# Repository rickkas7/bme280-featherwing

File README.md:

# BME280 FeatherWing with Grove

*FeatherWing with a BME280 temperature, humidity, and pressure sensor. And Grove connectors.*

This is a simple board that includes a BME280 temperature, humidity, and pressure sensor, connected by I2C (pins D0 and D1). Since the chip is really tiny, it also includes [Grove connectors](http://wiki.seeedstudio.com/Grove_System/) so you can attach other analog, digital, or I2C sensors with a 4-pin Grove cable.

## What You Need

This is a somewhat advanced project mainly because the BME280 is tiny and has pads on the bottom of the module, making it impossible to solder by hand. You'll need a SMD reflow oven to do it effectively.

- Circuit boards (I order them from [OshPark](https://oshpark.com))
- Stencil (this board can be assembled without one, but I order them from [OshStencils](https://oshstencils.com))
- Solder paste
- Reflow oven (the inexpensive [T962](https://www.amazon.com/dp/B01LZYEF90/ref=dp_prsubs_1) works fine)
- Soldering iron (for the header pins and Grove connectors)
- Regular solder

## Eagle Directory

- FeatherBME280.sch Schematic for Eagle CAD (also available in pdf)
- FeatherBME280.pdf Schematic in pdf
- FeatherBME280.brd Board Layout in Eagle CAD
- FeatherBME280.lbr Library file with all components in the board

## BOM

| Quantity | Item | Example |
| --- | --- | --- |
| 1 | 0.1µF capacitor 0603 | [Murata GRM188R71C104KA01D](https://www.digikey.com/product-detail/en/murata-electronics-north-america/GRM188R71C104KA01D/490-1532-1-ND/587771) |
| 2 | 10KΩ resistor 0603 | [Panasonic ERJ-PA3J103V](https://www.digikey.com/product-detail/en/panasonic-electronic-components/ERJ-PA3J103V/P10KBZCT-ND/5036237) | 
| 1 | BME280 | [BME280](https://www.digikey.com/product-detail/en/bosch-sensortec/BME280/828-1063-1-ND/6136314) |
| 4 | Grove Connectors | [Grove connector](https://www.digikey.com/product-detail/en/seeed-technology-co-ltd/110990030/1597-1082-ND/5482560) |
| | Male header pins 0.1" | [Sullins PRPC040SAAN-RC](https://www.digikey.com/product-detail/en/PRPC040SAAN-RC/S1011EC-40-ND/2775214) |

## Firmware

In order to use the BME280 sensor, you can use the [Adafruit\_BME280\_RK](https://github.com/rickkas7/Adafruit_BME280_RK) library. Follow the i2c_bme280 example as this board uses the BME280 in I2C mode.

Example:

```
#include "Adafruit_BME280_RK.h"

#define SEALEVELPRESSURE_HPA (1013.25)

Adafruit_BME280 bme; // I2C

unsigned long delayTime;

void printValues();

void setup() {
    Serial.begin(9600);
    Serial.println("BME280 test");

    bool status;
    
    // Address is either 0x76 or 0x77. If omitted, the default is 0x77.
    status = bme.begin(0x76);
    if (!status) {
        Serial.println("Could not find a valid BME280 sensor, check wiring!");
        while (1);
    }
    
    Serial.println("-- Default Test --");
    delayTime = 1000;

    Serial.println();
}

void loop() { 
    printValues();
    delay(delayTime);
}

void printValues() {
    Serial.print("Temperature = ");
    Serial.print(bme.readTemperature());
    Serial.println(" *C");

    Serial.print("Pressure = ");

    Serial.print(bme.readPressure() / 100.0F);
    Serial.println(" hPa");

    Serial.print("Approx. Altitude = ");
    Serial.print(bme.readAltitude(SEALEVELPRESSURE_HPA));
    Serial.println(" m");

    Serial.print("Humidity = ");
    Serial.print(bme.readHumidity());
    Serial.println(" %");

    Serial.println();
}

```

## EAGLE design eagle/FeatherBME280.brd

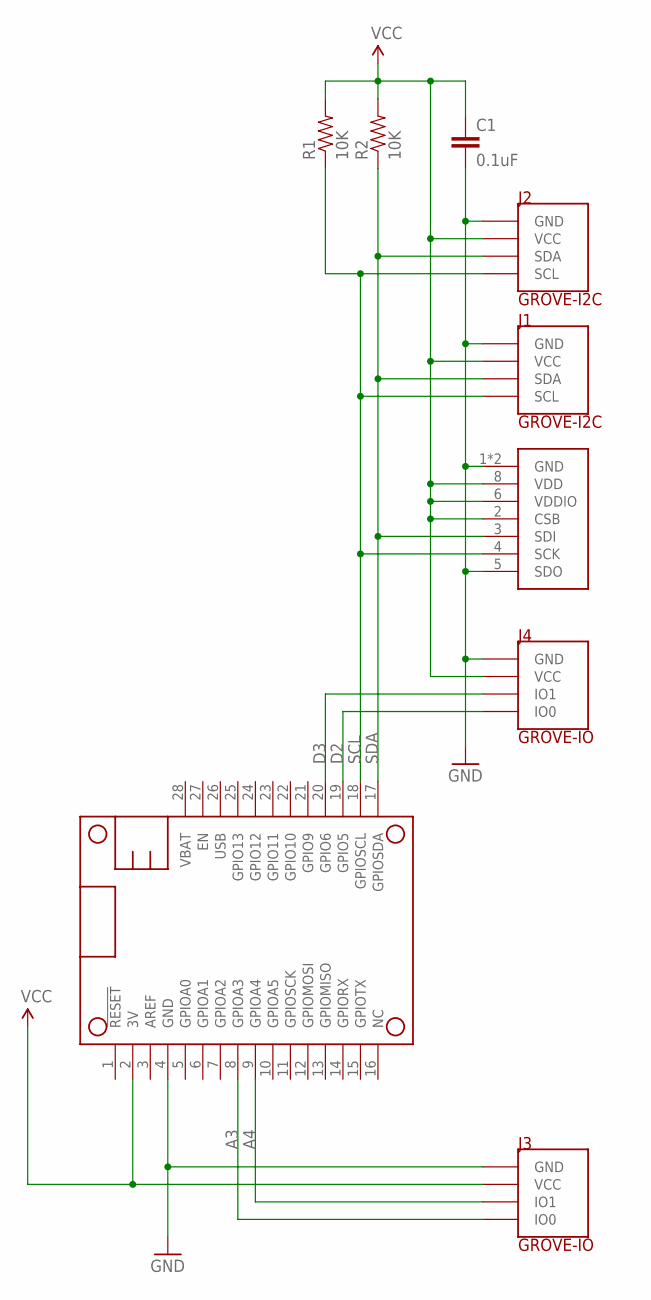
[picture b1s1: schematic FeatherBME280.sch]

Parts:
C1: 0.1uF; 0603-CAP
J1, J2: GROVE-I2C; GROVE-VERT-PTH
J3, J4: GROVE-IO; GROVE-VERT-PTH
MS1: FEATHERWING
R1, R2: 10K; 0603-RES
U$1: BME280

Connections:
A3: J3.1 (IO0), MS1.8 (GPIOA3)
A4: J3.2 (IO1), MS1.9 (GPIOA4)
D2: J4.1 (IO0), MS1.19 (GPIO5)
D3: J4.2 (IO1), MS1.20 (GPIO6)
GND: C1.2, J1.4 (GND), J2.4 (GND), J3.4 (GND), J4.4 (GND), MS1.4 (GND), U$1.1 (GND), U$1.5 (SDO), U$1.7 (GND)
SCL: J1.1 (SCL), J2.1 (SCL), MS1.18 (GPIOSCL), R1.1, U$1.4 (SCK)
SDA: J1.2 (SDA), J2.2 (SDA), MS1.17 (GPIOSDA), R2.1, U$1.3 (SDI)
VCC: C1.1, J1.3 (VCC), J2.3 (VCC), J3.3 (VCC), J4.3 (VCC), MS1.2 (3V), R1.2, R2.2, U$1.2 (CSB), U$1.6 (VDDIO), U$1.8 (VDD)

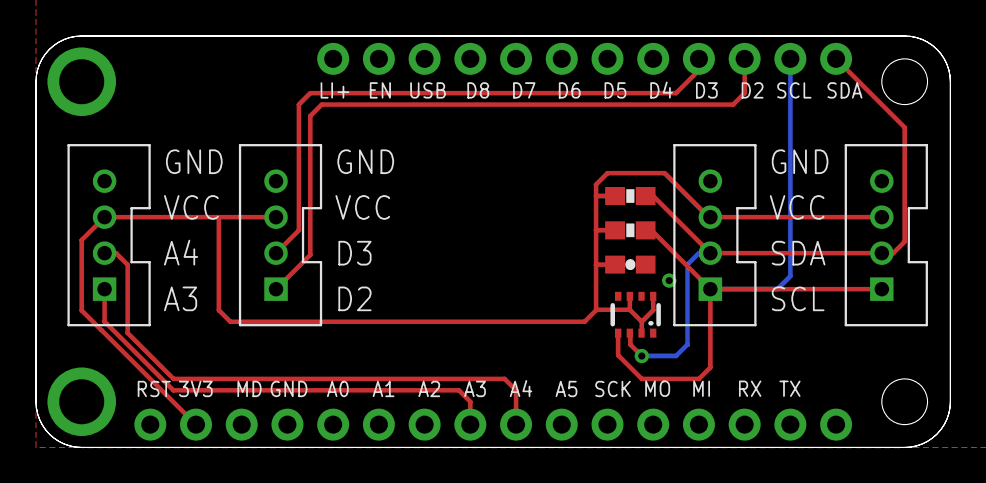
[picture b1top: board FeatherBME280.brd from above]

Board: 2 copper layers, 50.8 x 22.9 mm, 9 parts (0 on the bottom side), 8 nets.

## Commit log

2019-03-14 Initial checkin
